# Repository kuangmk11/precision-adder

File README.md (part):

# Precision Adder v2.2
This is a precision CV source and adder. It has four stages, each with an input, an output and a passthru. Each stage's **output** normals down to the next stage's input, so with a single cable into `IN1` the stages cascade and their offsets sum; patching into any `IN` breaks the normal above it. The passthru is a buffered copy of that stage's input, so with nothing patched `PT2` = `OUT1`, `PT3` = `OUT2`, and so on.

Each section provides a different voltage to be added to the input: +/- 2v, +/- 1v, +/- .5833333v (a fifth), +/- .4166666v (a fourth)

## The v2.2 reference build

Everything shipped for the built v2.2 board now lives in [`reference/`](reference/): its
schematic PDF, the three gerber archives, the EasyEDA bill of materials and the photos
above. That revision is finished and is not being changed — the directory is there so the
built design stays available for anyone assembling a v2.2, and as the thing v3 is measured
against.

Two v2.2 documents deliberately stay outside it. [`docs/v2.2-topology.md`](docs/v2.2-topology.md)
is the ladder maths read off the v2.2 schematic, and it is a live input to v3 rather than an
artifact of the old build — `tools/gen_schematic.py` works from it, and `docs/v3-BOM.md`
verifies against it. [`docs/DESIGN-LOG.md`](docs/DESIGN-LOG.md) spans both revisions.

## Available intervals

The switches are SPDT ON-ON, so a stage in the chain always contributes either its positive or its negative offset — there's no center-off. Using the switches alone gives 4 stages x 2 states = **16 combinations** and 13 distinct voltages.

A stage can also be bypassed by patching its `PT` (passthru) into the `IN` of the next stage, feeding that stage's input forward instead of its output. That makes each stage a 3-state element (**+**, **-**, or **bypassed**), for **81 configurations** and **39 distinct voltages**.

The full set is symmetric, so the table below lists magnitudes only — for the negative of any row, flip every `+`/`-` (bypasses stay bypassed). `o` = stage bypassed.

| Semitones | Volts | Interval | Settings (2oct · 1oct · 5th · 4th) |
|---:|---:|---|---|
| 48 | 4.0000 | 4 oct | `+ + + +` |
| 43 | 3.5833 | 3 oct + 5th | `+ + + o` |
| 41 | 3.4167 | 3 oct + 4th | `+ + o +` |
| 38 | 3.1667 | 3 oct + M2 | `+ + + -` |
| 36 | 3.0000 | 3 oct | `+ + o o` · `+ o + +` |
| 34 | 2.8333 | 2 oct + m7 | `+ + - +` |
| 31 | 2.5833 | 2 oct + 5th | `+ + o -` · `+ o + o` |
| 29 | 2.4167 | 2 oct + 4th | `+ + - o` · `+ o o +` |
| 26 | 2.1667 | 2 oct + M2 | `+ o + -` |
| 24 | 2.0000 | 2 oct | `+ + - -` · `+ o o o` · `+ - + +` · `o + + +` |
| 22 | 1.8333 | 1 oct + m7 | `+ o - +` |
| 19 | 1.5833 | 1 oct + 5th | `+ o o -` · `+ - + o` · `o + + o` |
| 17 | 1.4167 | 1 oct + 4th | `+ o - o` · `+ - o +` · `o + o +` |
| 14 | 1.1667 | 1 oct + M2 | `+ - + -` · `o + + -` |
| 12 | 1.0000 | 1 oct | `+ o - -` · `+ - o o` · `o + o o` · `o o + +` |
| 10 | 0.8333 | m7 | `+ - - +` · `o + - +` |
| 7 | 0.5833 | 5th | `+ - o -` · `o + o -` · `o o + o` |
| 5 | 0.4167 | 4th | `+ - - o` · `o + - o` · `o o o +` |
| 2 | 0.1667 | M2 | `o o + -` |
| 0 | 0.0000 | unison | `o o o o` · `+ - - -` · `o + - -` · `o - + +` · `- + + +` |

### The pattern

Every reachable offset is **0, ±2, or ±5 semitones (mod 12)** — unison, M2, 4th, 5th, m7, and their octaves. Within ±48 semitones every such value is reachable *except* ±46. Thirds, tritones, sixths, and single semitones are not available, because a fifth and a fourth can only ever combine to an octave (7+5) or a whole step (7-5).

The usable pitch-class set is therefore the suspended pentatonic `{0, 2, 5, 7, 10}`, spread across a full ±4 octaves in 1/12 V steps.

### Patching notes

- **Leading bypasses are free** — plug your CV into `IN2` / `IN3` / `IN4` instead of `IN1`.
- **Trailing bypasses are free** — take your output from the last active stage's `OUT` instead of `OUT4`.
- **Only interior bypasses cost a cable**: one patch, `PTn` -> `IN(n+1)`, per skipped stage.
- Where a row lists multiple settings, prefer the one with bypasses at the edges — same voltage, fewer cables. For example 2 oct + 4th is `+ + - o` with no cables, versus `+ o o +` with two.

## v3 proposal (unbuilt)

v2.2 is a serial interval adder with a redundant interval set. v3 keeps the cascade, fixes the set, and reorganises the panel around what the cascade is actually good at — stacking intervals into chords.

The interval problem first: because a fifth plus a fourth is exactly an octave (7 + 5 = 12), two of v2.2's four stages collapse into a redundant third. 81 configurations produce only 39 distinct voltages, and the output can never leave the pitch classes `{0, 2, 5, 7, 10}` — no thirds, no sixths, no tritone, no single semitones.

### Four changes

**1. ON-OFF-ON switches.** v2.2 uses SPDT ON-ON, which is why bypassing a stage costs a patch cable. A subminiature ON-OFF-ON is the same footprint at essentially the same price, and the center detent gives each stage a native off position. Every configuration becomes reachable from the front panel with no patching. (Doepfer's A-185-2 has always done it this way — see the comparison below.)

**2. Drop `IN2`-`IN4` and `PT2`-`PT4`.** Outputs normal down to the next input, so with nothing patched `PT2` = `OUT1`, `PT3` = `OUT2`, `PT4` = `OUT3`. Those passthrus are duplicates of the output above them. The extra inputs existed to break the cascade, which the center-off switch now does better. Six jacks were doing the work of two.

**3. Sum three inputs at the front.** `IN1` + `IN2` + `IN3` at unity gain feed the head of the cascade. This is the multi-source summing the module is named for — keyboard plus sequencer plus offset — and it is what the freed panel space buys. `PT` becomes the buffered *sum* of the inputs: an untransposed root that stays put while the cascade transposes everything above it.

**4. Collapse the two octave stages into one, and make stages 2-4 thirds.** Stage 1 becomes a 5-state octave control (±1, ±2, off) from two toggles, freeing a stage. Stages 2 and 3 get a three-position quality switch selecting **4th / maj 3rd / min 3rd**, and stage 4 selects **5th / maj 3rd / min 3rd** — because stacked thirds are how chords are built, and the fifth on the last stage keeps the module's most-used interval one flip away.

### Panel

| | v2.2 | v3 |
|---|---:|---:|
| Jacks | 12 | 8 — `IN1` `IN2` `IN3` `PT` `OUT1`-`OUT4` |
| Switches | 4 | 8 — 2 per stage |
| **Positions** | **16** | **16** |

Same density as the board already built. No rotary, no new mechanical problem.

**This is a new panel, not v2.2's reused.** Earlier v3 drafts kept every v2.2 hole
position and only reassigned diameters, which forced the four outputs into two shared
rows. Grouping each stage instead — its two switches and its own output, boxed together —
needs six evenly spaced rows below the inputs, so the positions are refitted. The v3 main
board is new anyway.

Panel and drawing are generated by [`tools/gen_panel.py`](tools/gen_panel.py) from one
layout table, so they cannot disagree:

```sh
python3 tools/gen_panel.py            # writes the .kicad_pcb and the .svg, with a clearance report
python3 tools/gen_panel.py --table    # the hole schedule below
```

- [`docs/v3-panel.kicad_pcb`](docs/v3-panel.kicad_pcb) — board outline, holes and mounting
  slots on `Edge.Cuts`, silkscreen on `F.SilkS`. Holes are `Edge.Cuts` circles, so the fab
  routes rather than drills them; swap to NPTH pads if your fab prefers.
- [`docs/v3-panel.svg`](docs/v3-panel.svg) — the same geometry at 1:1 (1 unit = 1 mm,
  20 × 128.5 mm), for printing and review. The grey rings are hardware footprints — 8 mm
  Thonkiconn nut, 7.5 mm toggle nut — shown for clearance checking, not artwork, and not
  in the KiCad output.

Conventions — lettering, marks, label placement, mounting — are in
[`PANEL_STYLE_v1.02.md`](PANEL_STYLE_v1.02.md).

#### How it reads

Four jacks at the top: three summed inputs and `SUM`, the buffered sum that `PT` becomes.
`SUM` is an output, so it carries the ring — the panel's only closed circle, which is what
lets direction read at a glance. The ring has to clear the 8 mm nut to be visible at all,
and a 20 mm panel carrying two 8 mm nuts has 4 mm of slack in total, so at r 4.4 it ends up
0.28 mm from the cut on the outboard side. Still on the board, but well inside the 0.6 mm
edge margin, and a fab may trim the outer edge of it. Taken deliberately: a broken ring
reads worse than a clipped one. Below them, **four boxed groups, one per stage — polarity
switch, selector switch, that stage's output.** Each stage now owns its output, which the
old shared-row layout could not manage.

**Arrows trace the cascade** across the top pair, down into the bottom-left group, and
across the bottom pair — the order the stages actually sum in. The middle leg cannot be a
straight diagonal: about 4 mm of clear band between the box rows against a 10.8 mm column
pitch would need a 15° line, and the house routing is 0°, 90° and 45° only. So it drops,
takes a 45° knee, runs the band and turns down into the group it feeds. Where an arrow
crosses a box outline the outline is broken, the same way a group name breaks it.

`OUT1`–`OUT4` do not repeat the ring. Each already sits inside a named box that says which
stage it belongs to, and the style guide's rule against a second closed circle is what
keeps `SUM`'s ring meaningful. If you would rather every output ring, it is one line in the
generator.

Within a group: `+` above the polarity toggle, `−` below it, and **`0` beside its centre
detent**. The selector's two throws are labelled above and below it the same way.

That `0` matters more than it looks. A selector displays a value at all times, so without
it the panel reads as though a stage adds its interval even when the stage is switched off
— and the polarity toggle's centre, not the selector's, is what turns a stage off. One rule
covers both toggles now: **a three-position toggle's centre value is marked in the strip
between its nut and the box edge.** `OCT`'s magnitude switch is two-position and has no
centre, so it carries no such mark.

It is also why a plain fifth is one flip. At rest every polarity toggle is centred and the
module passes through untouched, whatever the selectors show; move stage 4's polarity to
`+` and its selector is already sitting on the `5`.

**The selector's centre detent carries the stage's odd interval** — the 4th on the two
`3RD` stages, the 5th on `5TH` — and the two throws are the two thirds, `MAJ` and `MIN`.
That is partly ergonomic, since the thirds are the pair you reach for when building a
chord, and partly forced: the centre mark is the only one with nowhere to go but the
1.2 mm strip between the toggle nut and the box, where a single character fits and two do
not. It is set at 1.0 mm, below the house 1.6 mm minimum, and is the one deliberate
exception on the panel.

#### Hole schedule

Origin top-left, millimetres, Y down — the drawing's own frame, not the old gerbers'.

| Y (mm) | X (mm) | Ø | What |
|---:|---:|---:|---|
| 16.60 | 4.80 | 6.0 | IN1 |
| 16.60 | 15.20 | 6.0 | IN2 |
| 28.60 | 4.80 | 6.0 | IN3 |
| 28.60 | 15.20 | 6.0 | SUM (output, ringed) |
| 44.80 | 4.80 | 5.0 | OCT polarity  +/o/− |
| 44.80 | 15.20 | 5.0 | 3RD polarity  +/o/− |
| 57.80 | 4.80 | 5.0 | OCT select  1/2 |
| 57.80 | 15.20 | 5.0 | 3RD select  MAJ/MIN (detent 4) |
| 68.80 | 4.80 | 6.0 | OUT1 |
| 68.80 | 15.20 | 6.0 | OUT2 |
| 88.00 | 4.80 | 5.0 | 3RD polarity  +/o/− |
| 88.00 | 15.20 | 5.0 | 5TH polarity  +/o/− |
| 101.00 | 4.80 | 5.0 | 3RD select  MAJ/MIN (detent 4) |
| 101.00 | 15.20 | 5.0 | 5TH select  MAJ/MIN (detent 5) |
| 112.00 | 4.80 | 6.0 | OUT3 |
| 112.00 | 15.20 | 6.0 | OUT4 |
| 3.00 | 12.50 | 6.4×3.2 | mounting slot, obround |
| 125.50 | 7.50 | 6.4×3.2 | mounting slot, obround |

Mounting follows the style guide's ≤ 6 HP rule: one 6.4 × 3.2 mm horizontal slot top-right
and one bottom-left, so the module can slide ±1.6 mm to meet its neighbours and cannot
pivot on a single screw per rail. v2.2's round Ø3.2 holes do not carry over.

#### What the generator checks, and what it cannot

`gen_panel.py` refuses to write if anything overlaps, and reports the tightest clearance in
each category. Currently: **0.15 mm** text-to-nut, **0.64 mm** text-to-text, **0.15 mm**
text-to-silk, **0.42 mm** text-to-ring, **0.60 mm** silk-to-edge, **1.40 mm** of material
at the worst hole, and **2.40 mm** between the closest two nuts. `SUM`'s ring is exempted
from the edge margin and reported separately, so the exception stays visible instead of
being absorbed into a looser rule.

Those come from a stroke-glyph model that assumes ink fills 0.62 em of each character
cell — conservative for the KiCad stroke font, but still a model. **KiCad's own DRC passes
with 0 violations and 0 unconnected items** (`tools/kicad-check.sh`), and the board plots
correctly from KiCad, mounting slots and all.

The two toggles in a group are 13.0 mm apart, leaving 5.5 mm between their nuts — up from
4.9 mm in the row-based draft, but still unproven on this hardware, since v2.2 stacks no
toggles at all. Print the SVG at 100%, check it measures 20 × 128.5 mm, and try the pairs
with real fingers.

### Schematic

[`docs/v3-adder.kicad_sch`](docs/v3-adder.kicad_sch), generated by
[`tools/gen_schematic.py`](tools/gen_schematic.py) from a netlist table:

```sh
python3 tools/gen_schematic.py             # writes the .kicad_sch, with a design report
python3 tools/gen_schematic.py --bom       # bill of materials
python3 tools/gen_schematic.py --netlist   # every net and what is on it
```

**It is a scaffold, not a finished drawing.** Connectivity is complete and correct;
placement is a plain grid, and every connection is made with a net label on a short pin stub
rather than by routing wires. That is deliberate — label-based connectivity cannot be got
subtly wrong the way routed wires can, and rearranging symbols in KiCad afterwards breaks
nothing. Expect to spend time on layout, not on wiring.

Topology follows [`docs/v2.2-topology.md`](docs/v2.2-topology.md). The reference block, the
power block and the summing topology are v2.2's, unchanged. 102 parts, 72 nets, 12 op-amp
channels across three OPA4196 — 11 used, one spare tied off as a follower.

**Only the lower ladder segments need to be precise.** A tap's voltage is set by the ratio
of the segments below it to the whole chain, and the trimmer sits in series at the top, so
the top segment's absolute value is absorbed by trimming — which is why the BOM shows
5.5k, 24.5k and 22.5k and why that does not matter. Use the nearest E96 part and let the
trimmer take up the difference. What does matter is the ratio between the small segments
(1k, 3k, 12k), and that is where hand-matched parts earn their keep.

Alongside the schematic the generator writes `adder.kicad_sym`, `v3-adder.kicad_pro` and a
`sym-lib-table`, so the project opens with its symbol library resolved rather than warning
once per symbol.

**KiCad's own ERC passes with 0 errors.** Run it yourself:

```sh
KICAD_CLI="/path/to/kicad-cli" tools/kicad-check.sh    # ERC, DRC and plots into .kicadcheck/
```

The 23 remaining ERC warnings are all `footprint_link_issues` on the custom parts — jacks,
toggles, trimmers, ferrites, the Eurorack header. Those footprints are yours to supply, and
a name that does not resolve is a more honest placeholder than a wrong one that does. Stock
KiCad footprints are used everywhere they exist, so the passives, op-amps, regulators and
diodes resolve on any install.

### Bill of materials

[`docs/v3-BOM.md`](docs/v3-BOM.md) is the parts list, with the tolerance reasoning for every
line. [`docs/BOM_v3_DigiKey.csv`](docs/BOM_v3_DigiKey.csv) alongside it is an upload-ready
DigiKey list covering 93 of the parts; its sourcing notes are the last section of `v3-BOM.md`.

Three things are worth knowing before ordering. The **E24 values this design depends on are
stocked in 0.1 %** — Panasonic's ERA-8 series has both the 3.00k and the 12.0k, so choosing E24
over E96 for the exact 3:1 ratio costs nothing in availability. The **ON-ON-ON DPDT has no
DigiKey equivalent** in this form factor and must come from a synth DIY shop, along with the
jacks and the axial ferrites. And **C9/C10 need a decision**: the MnO2 tantalum that satisfies
the ESR requirement is a surface-mount part, which does not fit the through-hole footprint the
BOM currently specifies for them.

#### Switches

Taiway series 200 subminiature throughout — `T1` actuator, `B1` bushing, `M2` PC thru-hole,
`Q` silver, `E` epoxy:

| Function | Part | Used for |
|---|---|---|
| SPDT ON-OFF-ON | `200-MSP3-T1B1M2QE` | polarity, ×4 |
| SPDT ON-ON | `200-MSP1-T1B1M2QE` | `OCT` magnitude, ×1 |
| DPDT ON-ON-ON | `200-MDP6-T1B1M2QE` | quality selectors, ×3 |

The `B1` bushing is **10-48 UNS, Ø4.80** and Taiway's recommended panel hole is **Ø4.95** —
the panel's Ø5.0 is right. There is also an optional 4.55 mm flat in the hole for
anti-rotation, which the panel does not cut, so the switches are held by nut torque alone.

**A DPDT ON-ON-ON is a 1-of-3 selector only if you cascade its poles.** Pins 1‑2‑3 are pole
A with 2 common, 4‑5‑6 are pole B with 5 common. Pole A's common is the output; one of its
throws is a tap outright, the other feeds pole B's common, and pole B picks between the
remaining two. Tying the commons together instead would short two ladder taps in every
position.

`MDP-6`'s contact sequence, from Taiway:

| Position | Contacts |
|---|---|
| 1 | `2-3, 5-6` |
| 2 (centre) | `2-3, 5-4` |
| 3 | `2-1, 5-4` |

`ONONON_VARIANT = 1` in `tools/gen_schematic.py` encodes exactly this. `check_selector()`
walks each selector through all three positions from that table and asserts the output
reaches the intended tap and **exactly one** tap — the property that makes the cascade
trustworthy, since getting it wrong shorts two points of a resistor ladder rather than
failing loudly. Setting the variant to 2 makes it fail at the centre detent, as it should.

PC-mount terminals are on a **5.08 × 2.54 mm** grid, six pins, numbered 6‑5‑4 down one
column and 3‑2‑1 down the other.

**Orientation does not matter.** The body is symmetric, so fitting it 180° round swaps
diagonally opposite pads (6↔1, 5↔2, 4↔3) *and* reverses the lever — and those two cancel
exactly. Read against the board's own pad numbers from lever-up to lever-down, the sequence
is unchanged. The pin numbers on a reversed part are wrong; its behaviour is not.
`check_rotation_symmetry()` asserts this against the contact table, so it stays true if the
table is ever edited.

The generator additionally checks, before writing: every `lib_id` resolves as a full
`library:name` string and every instantiated unit has a matching body; every pin coordinate
read back out of the written file lands on a wire endpoint, so the label stubs really do
attach; no pin is unconnected; no net has fewer than two connections; no reference is used
twice and no pin appears on two nets; and every ladder tap computes to its interval voltage
exactly with the trimmer centred.

### Stages

Read the selector column as **up / _centre detent_ / down**, which is how the panel is
marked: the two throws are the thirds, the detent is the stage's odd interval.

| Stage | Panel group | Control | Selects — up / _detent_ / down | Values | Volts |
|---|---|---|---|---|---|
| 1 | `OCT` | on-off-on + `1/2` on-on | 1 oct / — / 2 oct | ±12, ±24 st | 1.000000 / 2.000000 |
| 2 | `3RD` | on-off-on + quality on-on-on | M3 / _4th_ / m3 | ±4, ±5, ±3 st | 0.333333 / 0.416667 / 0.250000 |
| 3 | `3RD` | on-off-on + quality on-on-on | M3 / _4th_ / m3 | ±4, ±5, ±3 st | 0.333333 / 0.416667 / 0.250000 |
| 4 | `5TH` | on-off-on + quality on-on-on | M3 / _**5th**_ / m3 | ±4, ±7, ±3 st | 0.333333 / 0.583333 / 0.250000 |

The values are unchanged from earlier drafts — only which throw carries which. Stage 1's
magnitude switch is a two-position ON-ON, so it has no detent.

Stage 4 takes a **5th** where stages 2 and 3 take a 4th. That buys back the one-switch fifth — the module's most-used interval — and on the chord side it turns stage 4 into an extension selector, since stages 2 and 3 have already built the triad by the time the signal reaches it.

**1715 configurations, 83 distinct voltages, fully chromatic across ±41 semitones (±3.42 octaves), all 12 pitch classes.**

### Chords

The cascade means each output is a running sum, so `OUT1`-`OUT4` are stacked intervals, with `PT` available as an untransposed root beneath them. **Stages 2 and 3 set the triad; stage 4 sets the extension.**

| Triad (st2 + st3) | st4 = m3 | st4 = M3 | st4 = 5th |
|---|---|---|---|
| M3 + m3 — **major** | dominant 7th | major 7th | add9 |
| m3 + M3 — **minor** | minor 7th | minor-major 7th | minor add9 |
| m3 + m3 — **diminished** | diminished 7th | half-diminished | dim add b9 |
| M3 + M3 — **augmented** | augmented maj7 | augmented (8ve) | augmented #9 |

Twelve voicings from three switches, and the triad is already correct on `OUT1`-`OUT3` before stage 4 is touched. The 4th position on stages 2 and 3 adds sus and quartal voicings on top of that.

The `OCT` stage transposes the whole chord while `PT` holds the original root — so a pedal tone stays put underneath a transposed voicing.

This is what the old `{octave, 5th, 4th, maj 3rd}` set could not do: fifths and fourths do not stack into chords.

### Transposition chart

Taking `OUT4` as a single transposed voice. `o` = switch centered. Within any octave the settings are identical, so the `OCT` stage handles everything above; negative intervals are the mirror image.

| Semitones | Volts | Interval | OCT | st2 | st3 | st4 | Flips |
|---:|---:|---|:---:|:---:|:---:|:---:|---:|
| 0 | 0.0000 | unison | `o` | `o` | `o` | `o` | 0 |
| 1 | 0.0833 | min 2nd | `o` | `o` | `+4th` | `-M3` | 2 |
| 2 | 0.1667 | maj 2nd | `o` | `o` | `+4th` | `-m3` | 2 |
| 3 | 0.2500 | min 3rd | `o` | `o` | `o` | `+m3` | 1 |
| 4 | 0.3333 | maj 3rd | `o` | `o` | `o` | `+M3` | 1 |
| 5 | 0.4167 | 4th | `o` | `o` | `+4th` | `o` | 1 |
| 6 | 0.5000 | tritone | `o` | `o` | `+m3` | `+m3` | 2 |
| 7 | 0.5833 | 5th | `o` | `o` | `o` | `+5th` | **1** |
| 8 | 0.6667 | min 6th | `o` | `o` | `+4th` | `+m3` | 2 |
| 9 | 0.7500 | maj 6th | `o` | `o` | `+4th` | `+M3` | 2 |
| 10 | 0.8333 | min 7th | `o` | `o` | `+m3` | `+5th` | 2 |
| 11 | 0.9167 | maj 7th | `o` | `o` | `+M3` | `+5th` | 2 |
| 12 | 1.0000 | octave | `+1` | `o` | `o` | `o` | 1 |

Every interval up to the octave is one or two switch positions, and the octave, 4th, 5th, maj 3rd and min 3rd are all single flips. The remaining rows read as stacks — a tritone is two minor thirds, a major 7th is a major third over a fifth.

### Build notes

- **BOM:** 4x `SUBMINI_SPDT ON-OFF-ON` (polarity, one per stage), 3x `ON-ON-ON` DPDT (quality, stages 2-4), 1x `ON-ON` (octave magnitude). 8 jacks instead of 12.
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
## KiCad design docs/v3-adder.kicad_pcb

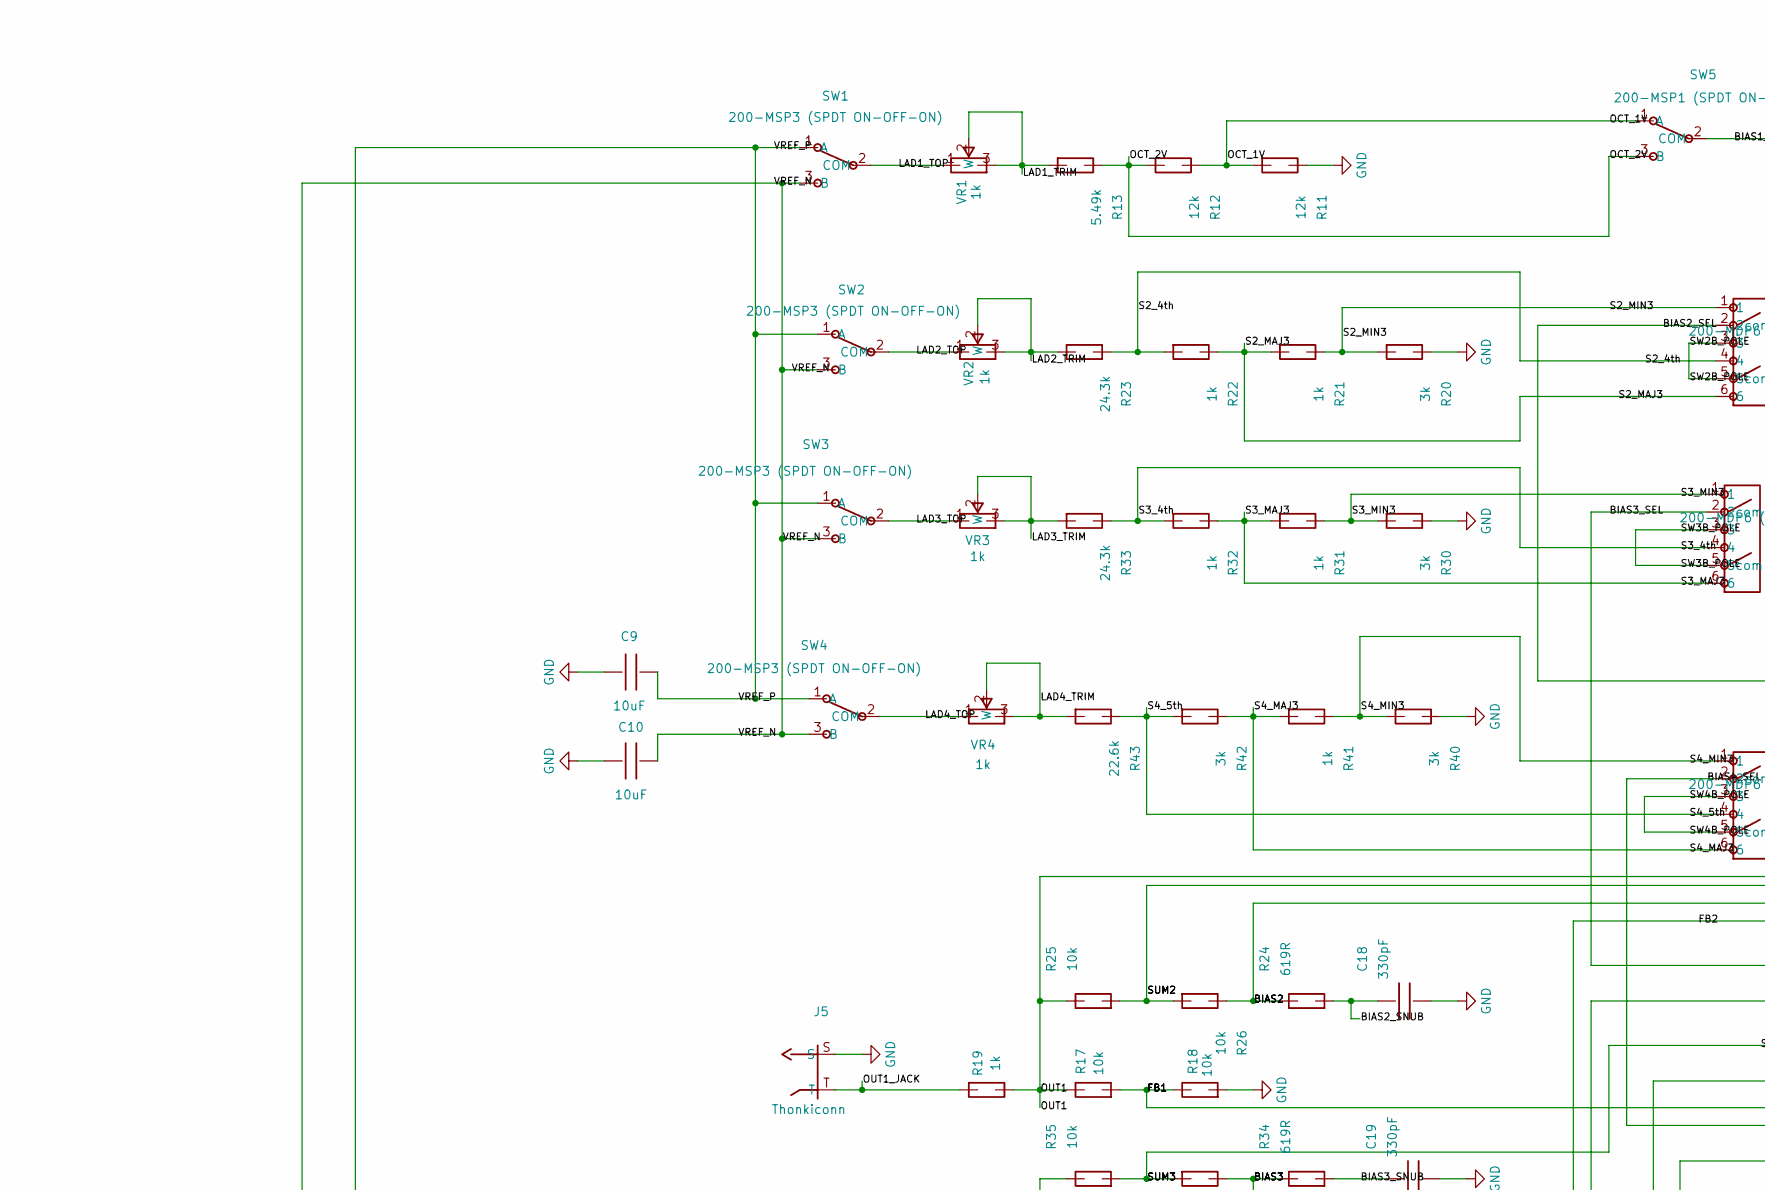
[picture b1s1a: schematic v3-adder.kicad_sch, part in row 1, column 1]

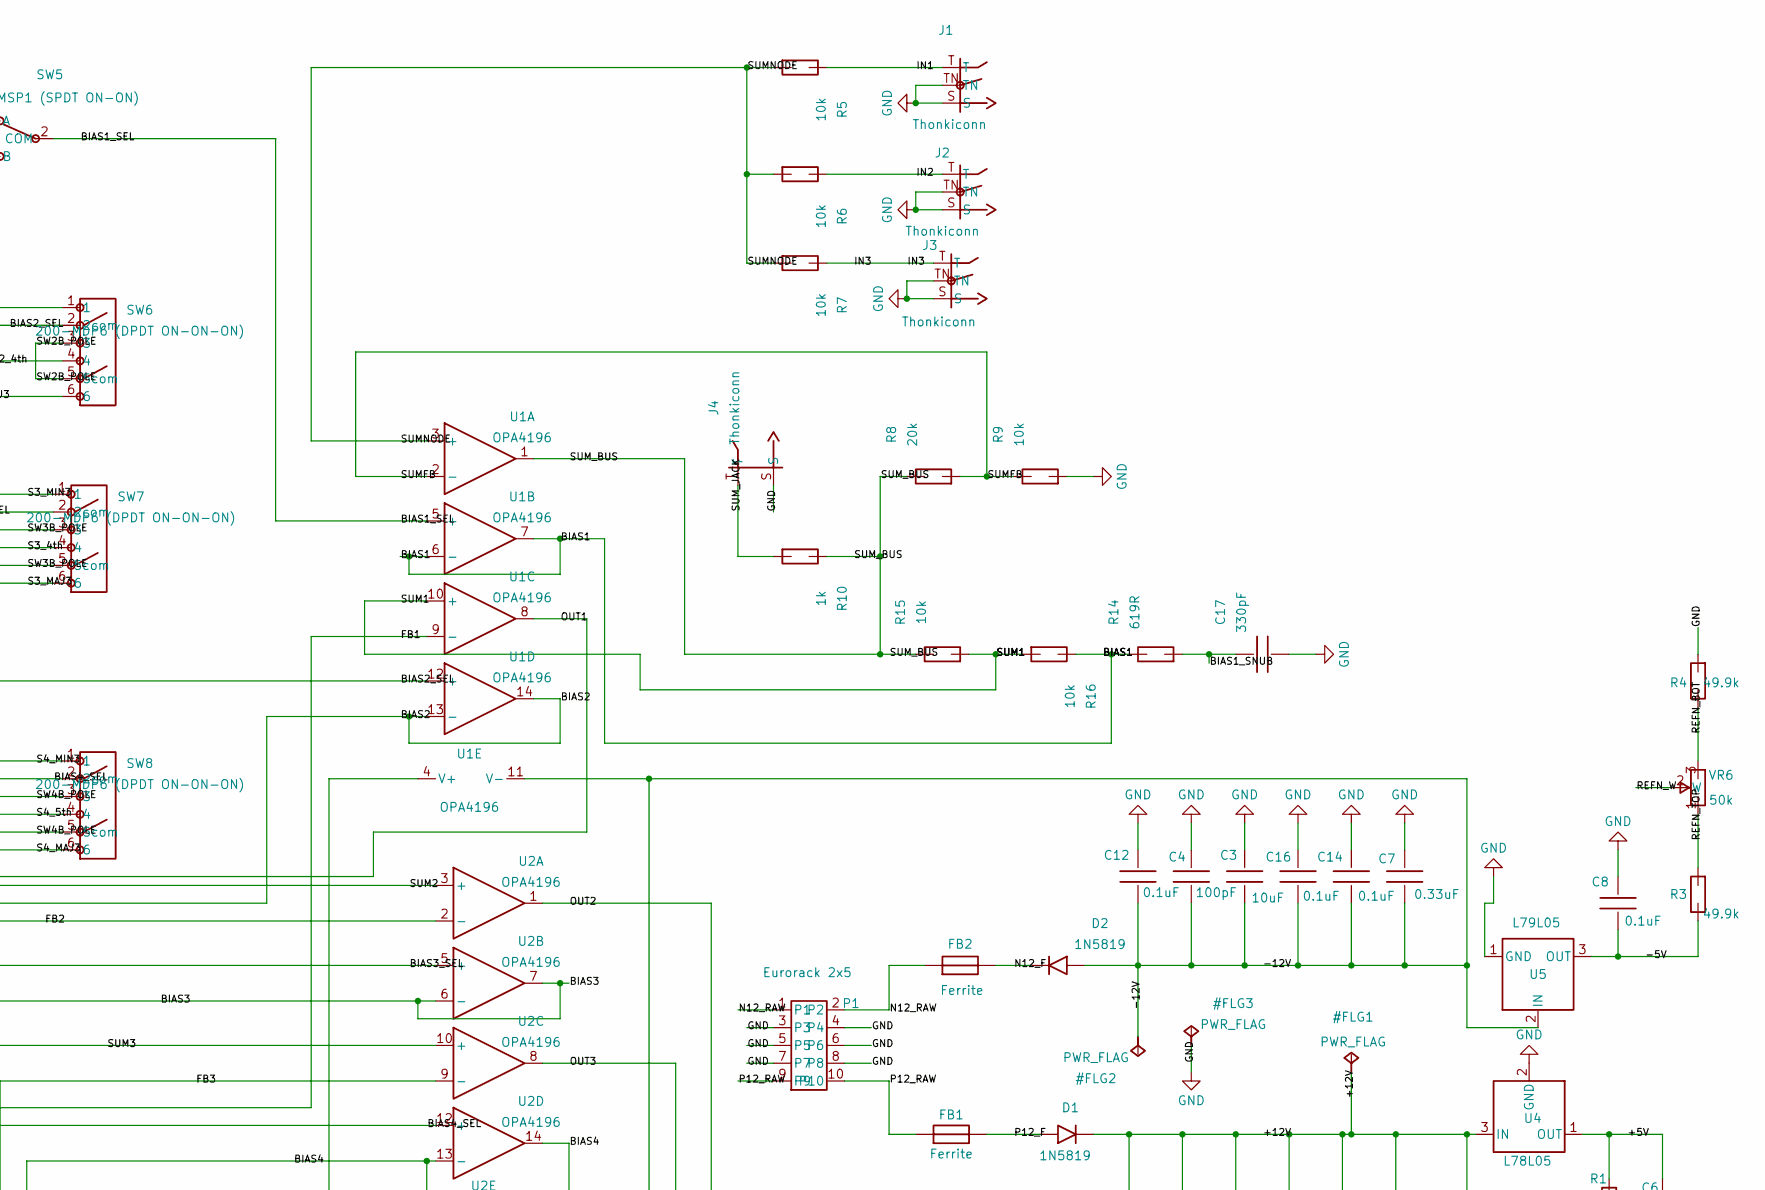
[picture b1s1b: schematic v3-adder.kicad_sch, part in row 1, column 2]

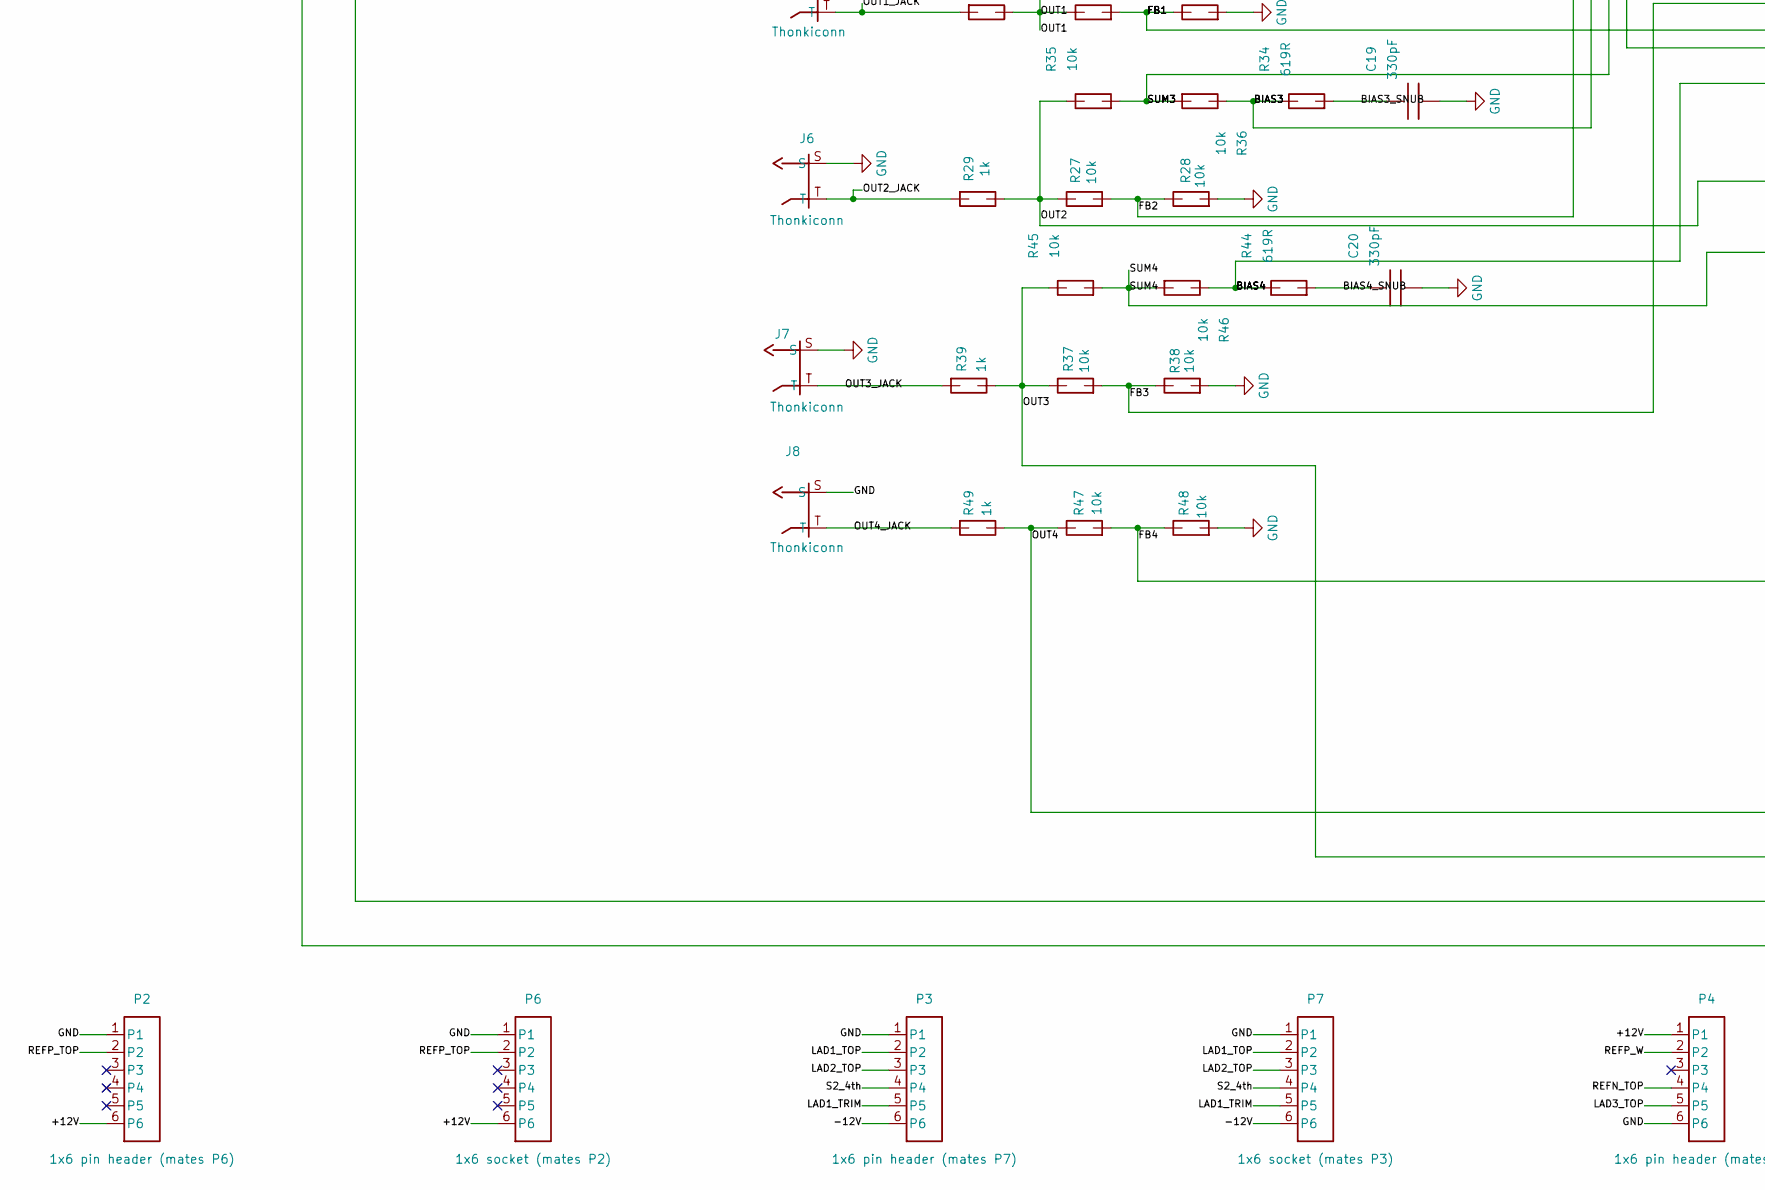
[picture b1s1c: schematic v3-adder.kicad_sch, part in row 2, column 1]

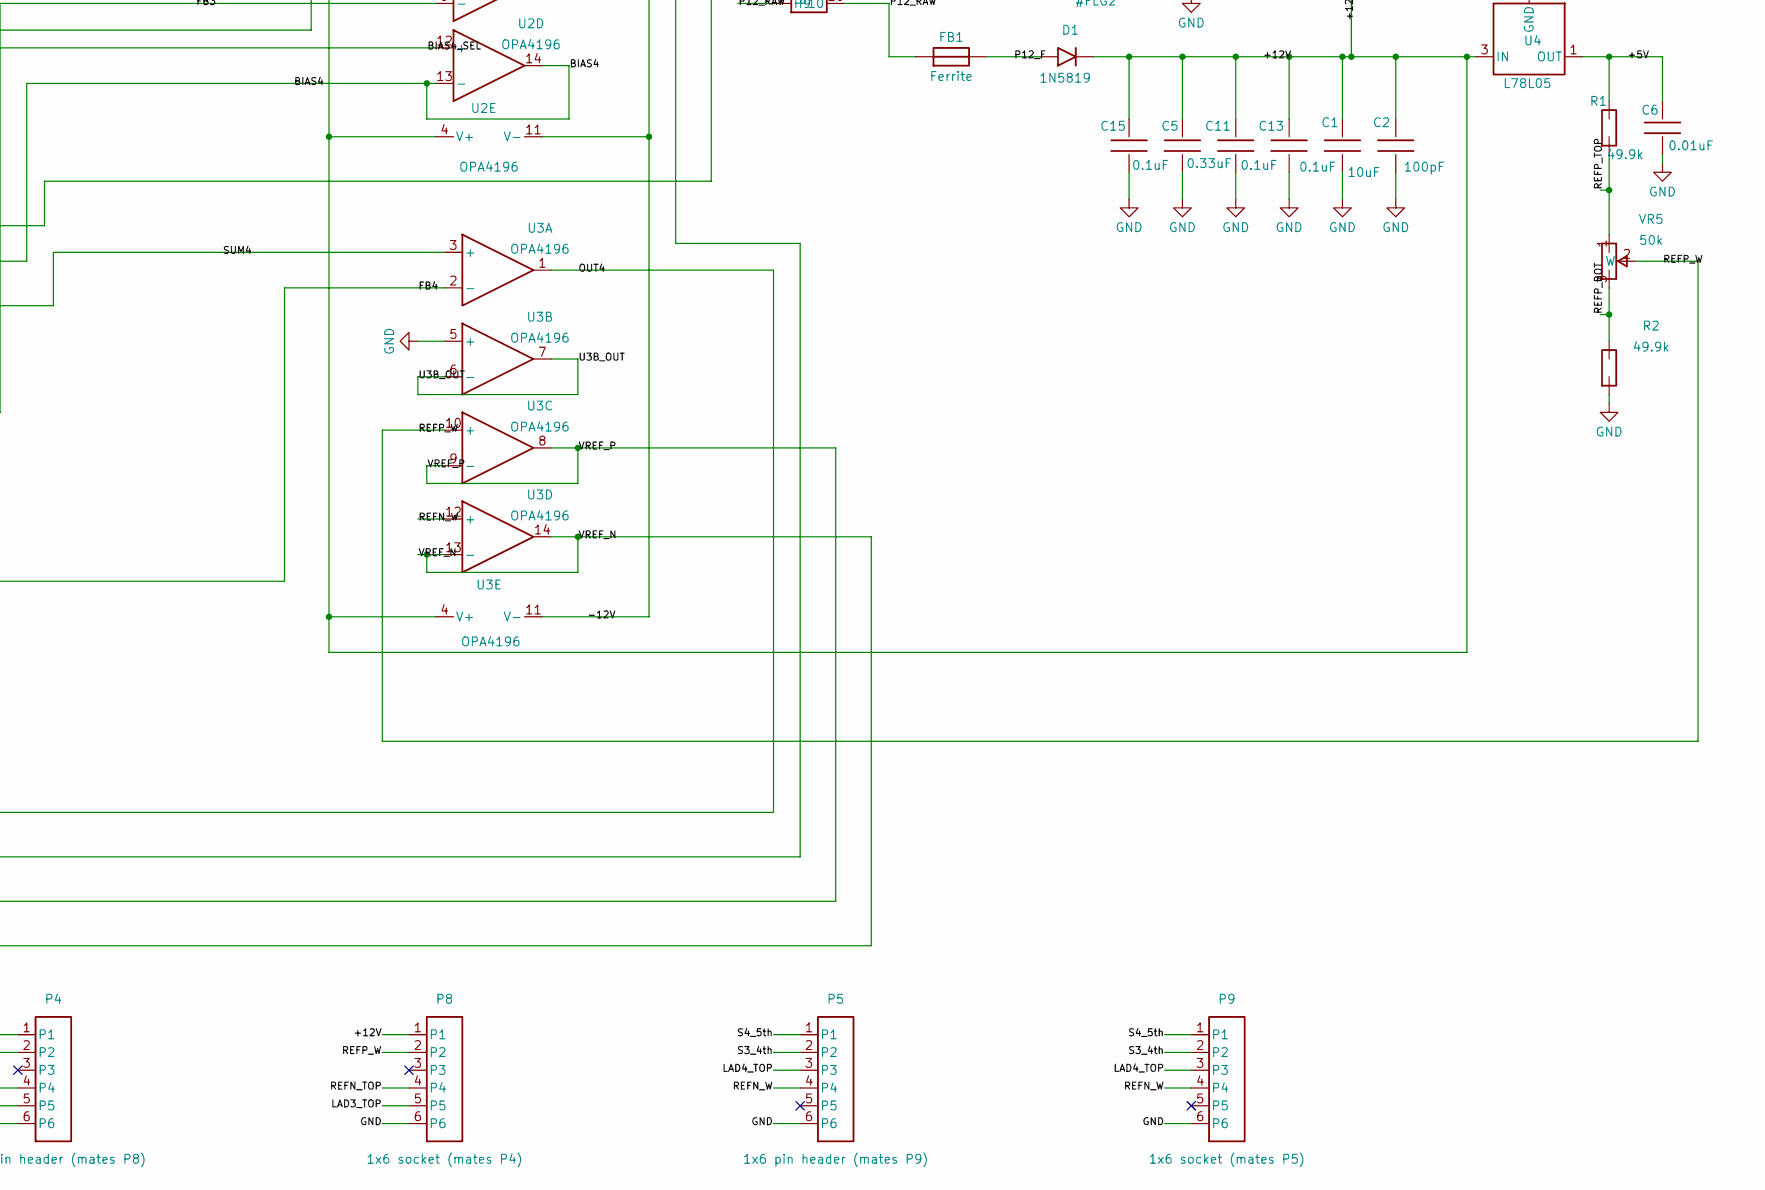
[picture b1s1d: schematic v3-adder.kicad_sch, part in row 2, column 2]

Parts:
C1, C3, C9, C10: 10uF; CP_Radial_D5.0mm_P2.00mm
C2, C4: 100pF; C_1206_3216Metric
C5, C7: 0.33uF; C_1206_3216Metric
C6: 0.01uF; C_1206_3216Metric
C8, C11, C12, C13, C14, C15, C16: 0.1uF; C_1206_3216Metric
C17, C18, C19, C20: 330pF; C_1206_3216Metric
D1, D2: 1N5819; D_DO-41_SOD81_P10.16mm_Horizontal
FB1, FB2: Ferrite; R_Axial_DIN0207_L6.3mm_D2.5mm_P7.62mm_Horizontal
J1, J2, J3, J4, J5, J6, J7, J8: Thonkiconn; Thonkiconn_PJ301M
P1: Eurorack 2x5; IDC-Header_2x05_P2.54mm_Vertical
P2: 1x6 pin header (mates P6); PinHeader_1x06_P2.54mm_Vertical
P3: 1x6 pin header (mates P7); PinHeader_1x06_P2.54mm_Vertical
P4: 1x6 pin header (mates P8); PinHeader_1x06_P2.54mm_Vertical
P5: 1x6 pin header (mates P9); PinHeader_1x06_P2.54mm_Vertical
P6: 1x6 socket (mates P2); PinSocket_1x06_P2.54mm_Vertical
P7: 1x6 socket (mates P3); PinSocket_1x06_P2.54mm_Vertical
P8: 1x6 socket (mates P4); PinSocket_1x06_P2.54mm_Vertical
P9: 1x6 socket (mates P5); PinSocket_1x06_P2.54mm_Vertical
R1, R2, R3, R4: 49.9k; R_1206_3216Metric
R5, R6, R7, R9, R15, R16, R17, R18, R25, R26, R27, R28, R35, R36, R37, R38, R45, R46, R47, R48: 10k; R_1206_3216Metric
R8: 20k; R_1206_3216Metric
R10, R19, R21, R22, R29, R31, R32, R39, R41, R49: 1k; R_1206_3216Metric
R11, R12: 12k; R_1206_3216Metric
R13: 5.49k; R_1206_3216Metric
R14, R24, R34, R44: 619R; R_1206_3216Metric
R20, R30, R40, R42: 3k; R_1206_3216Metric
R23, R33: 24.3k; R_1206_3216Metric
R43: 22.6k; R_1206_3216Metric
SW1, SW2, SW3, SW4: 200-MSP3 (SPDT ON-OFF-ON); SW_Taiway_200_SPDT
SW5: 200-MSP1 (SPDT ON-ON); SW_Taiway_200_SPDT
SW6, SW7, SW8: 200-MDP6 (DPDT ON-ON-ON); SW_Taiway_200_DPDT
U1, U2, U3: OPA4196; SOIC-14_3.9x8.7mm_P1.27mm
U4: L78L05; TO-92_Inline
U5: L79L05; TO-92_Inline
VR1, VR2, VR3, VR4: 1k; Potentiometer_Bourns_3296W_Vertical
VR5, VR6: 50k; Potentiometer_Bourns_3296W_Vertical

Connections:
/+5V: C6.1, R1.1, U4.1 (OUT)
/+12V: C1.1, C2.1, C5.1, C11.1, C13.1, C15.1, D1.1 (K), P2.6, P4.1, P6.6, P8.1, U1.4 (V+), U2.4 (V+), U3.4 (V+), U4.3 (IN)
/-5V: C8.1, R3.1, U5.3 (OUT)
/-12V: C3.1, C4.1, C7.1, C12.1, C14.1, C16.1, D2.2 (A), P3.6, P7.6, U1.11 (V-), U2.11 (V-), U3.11 (V-), U5.2 (IN)
/BIAS1: R14.1, R16.1, U1.6 (-), U1.7
/BIAS1_SEL: SW5.2 (COM), U1.5 (+)
/BIAS1_SNUB: C17.1, R14.2
/BIAS2: R24.1, R26.1, U1.13 (-), U1.14
/BIAS2_SEL: SW6.2 (2com), U1.12 (+)
/BIAS2_SNUB: C18.1, R24.2
/BIAS3: R34.1, R36.1, U2.6 (-), U2.7
/BIAS3_SEL: SW7.2 (2com), U2.5 (+)
/BIAS3_SNUB: C19.1, R34.2
/BIAS4: R44.1, R46.1, U2.13 (-), U2.14
/BIAS4_SEL: SW8.2 (2com), U2.12 (+)
/BIAS4_SNUB: C20.1, R44.2
/FB1: R17.2, R18.1, U1.9 (-)
/FB2: R27.2, R28.1, U2.2 (-)
/FB3: R37.2, R38.1, U2.9 (-)
/FB4: R47.2, R48.1, U3.2 (-)
/IN1: J1.T, R5.1
/IN2: J2.T, R6.1
/IN3: J3.T, R7.1
/LAD1_TOP: P3.2, P7.2, SW1.2 (COM), VR1.1
/LAD1_TRIM: P3.5, P7.5, R13.2, VR1.2 (W_2), VR1.3
/LAD2_TOP: P3.3, P7.3, SW2.2 (COM), VR2.1
/LAD2_TRIM: R23.2, VR2.2 (W_2), VR2.3
/LAD3_TOP: P4.5, P8.5, SW3.2 (COM), VR3.1
/LAD3_TRIM: R33.2, VR3.2 (W_2), VR3.3
/LAD4_TOP: P5.3, P9.3, SW4.2 (COM), VR4.1
/LAD4_TRIM: R43.2, VR4.2 (W_2), VR4.3
/N12_F: D2.1 (K), FB2.2
/N12_RAW: FB2.1, P1.1, P1.2
/OCT_1V: R11.2, R12.1, SW5.1 (A)
/OCT_2V: R12.2, R13.1, SW5.3 (B)
/OUT1: R17.1, R19.1, R25.1, U1.8
/OUT1_JACK: J5.T, R19.2
/OUT2: R27.1, R29.1, R35.1, U2.1
/OUT2_JACK: J6.T, R29.2
/OUT3: R37.1, R39.1, R45.1, U2.8
/OUT3_JACK: J7.T, R39.2
/OUT4: R47.1, R49.1, U3.1
/OUT4_JACK: J8.T, R49.2
/P12_F: D1.2 (A), FB1.2
/P12_RAW: FB1.1, P1.9, P1.10
/REFN_BOT: R4.1, VR6.3
/REFN_TOP: P4.4, P8.4, R3.2, VR6.1
/REFN_W: P5.4, P9.4, U3.12 (+), VR6.2 (W_2)
/REFP_BOT: R2.1, VR5.3
/REFP_TOP: P2.2, P6.2, R1.2, VR5.1
/REFP_W: P4.2, P8.2, U3.10 (+), VR5.2 (W_2)
/S2_4th: P3.4, P7.4, R22.2, R23.1, SW6.4
/S2_MAJ3: R21.2, R22.1, SW6.6
/S2_MIN3: R20.2, R21.1, SW6.1
/S3_4th: P5.2, P9.2, R32.2, R33.1, SW7.4
/S3_MAJ3: R31.2, R32.1, SW7.6
/S3_MIN3: R30.2, R31.1, SW7.1
/S4_5th: P5.1, P9.1, R42.2, R43.1, SW8.4
/S4_MAJ3: R41.2, R42.1, SW8.6
/S4_MIN3: R40.2, R41.1, SW8.1
/SUM1: R15.2, R16.2, U1.10 (+)
/SUM2: R25.2, R26.2, U2.3 (+)
/SUM3: R35.2, R36.2, U2.10 (+)
/SUM4: R45.2, R46.2, U3.3 (+)
/SUMFB: R8.2, R9.1, U1.2 (-)
/SUMNODE: R5.2, R6.2, R7.2, U1.3 (+)
/SUM_BUS: R8.1, R10.1, R15.1, U1.1
/SUM_JACK: J4.T, R10.2
/SW2B_POLE: SW6.3, SW6.5 (5com)
/SW3B_POLE: SW7.3, SW7.5 (5com)
/SW4B_POLE: SW8.3, SW8.5 (5com)
/U3B_OUT: U3.6 (-), U3.7
/VREF_N: C10.1, SW1.3 (B), SW2.3 (B), SW3.3 (B), SW4.3 (B), U3.13 (-), U3.14
/VREF_P: C9.1, SW1.1 (A), SW2.1 (A), SW3.1 (A), SW4.1 (A), U3.8, U3.9 (-)
GND: C1.2, C2.2, C3.2, C4.2, C5.2, C6.2, C7.2, C8.2, C9.2, C10.2, C11.2, C12.2, C13.2, C14.2, C15.2, C16.2, C17.2, C18.2, C19.2, C20.2, J1.S, J1.TN, J2.S, J2.TN, J3.S, J3.TN, J4.S, J5.S, J6.S, J7.S, J8.S, P1.3, P1.4, P1.5, P1.6, P1.7, P1.8, P2.1, P3.1, P4.6, P5.6, P6.1, P7.1, P8.6, P9.6, R2.2, R4.2, R9.2, R11.1, R18.2, R20.1, R28.2, R30.1, R38.2, R40.1, R48.2, U3.5 (+), U4.2 (GND), U5.1 (GND)

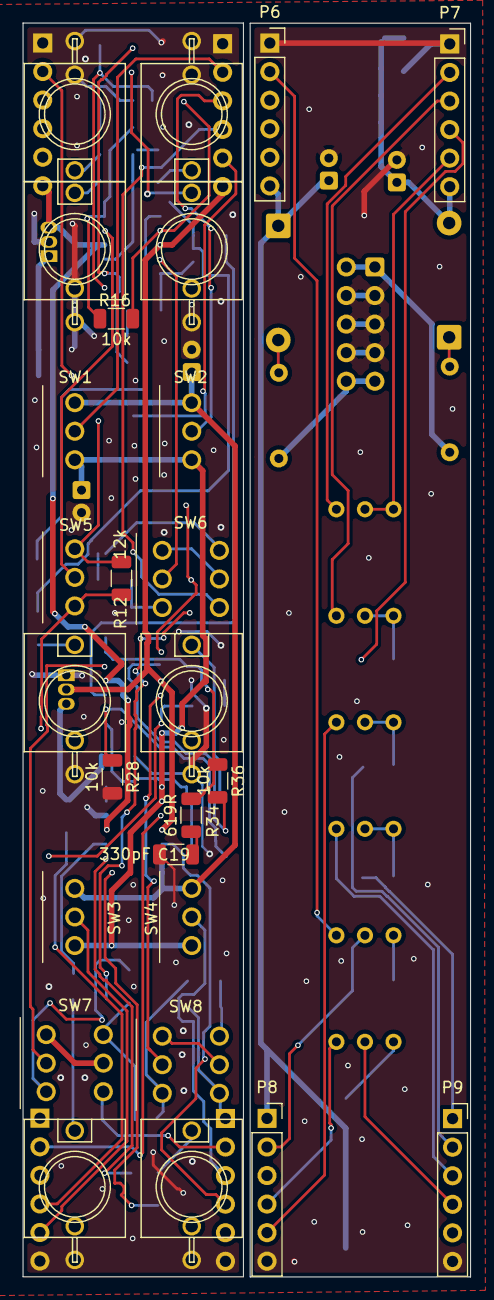
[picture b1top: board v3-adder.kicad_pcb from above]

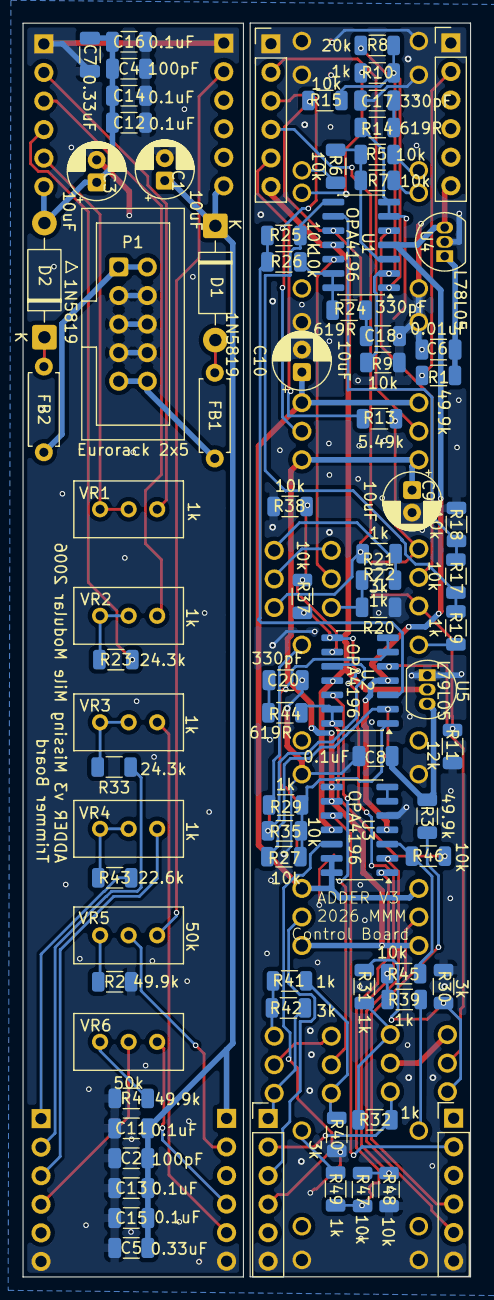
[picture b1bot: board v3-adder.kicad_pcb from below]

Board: 2 copper layers, 39.8 x 111.5 mm, 109 parts (83 on the bottom side), 75 nets.

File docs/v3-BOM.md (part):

# v3 bill of materials

Built for **hand assembly**: 1206 everywhere an SMD part is used, and through-hole kept for
anything that was already through-hole. 1206 is the largest size these values are commonly
stocked in, and the OPA4196's SOIC-14 is the largest package it comes in.

101 components. Values verified against the ladder maths in `v2.2-topology.md` — every
interval tap lands **exact to 0.000 cents** with these parts.

## Resistors

All 1206, `Resistor_SMD:R_1206_3216Metric`.

### 0.1 % — 32 parts

These set pitch directly. The per-stage trimmer corrects the chain's overall scale but
**not the ratios between taps**, so tolerance here is not recoverable.

| Qty | Value | Designators | Role |
|---:|---|---|---|
| 20 | 10.0k | R5–R7, R9, R15–R18, R25–R28, R35–R38, R45–R48 | input summing, per-stage summing and ×2 gain pairs |
| 5 | 1.00k | R21, R22, R31, R32, R41 | ladder segments |
| 4 | 3.00k | R20, R30, R40, R42 | ladder bottom segments |
| 2 | 12.0k | R11, R12 | `OCT` ladder — **match these two to each other** above all |
| 1 | 20.0k | R8 | input summer gain, ratio with R9 |

**3.00k and 12.0k are E24, not E96, and that is deliberate.** E96 has no exact 3:1 pair —
its nearest is 3.01k against 1.00k, which is a 0.33 % ratio error and puts the 4th out by
0.66 cents. Worse, that error cannot be selected away: a 0.1 % 3.01k never measures 3.000k.
E24 values are stocked in 0.1 % thin film, so use them.

`OCT` only needs its two segments **equal to each other** — the absolute value is free,
because the trimmer sets the scale and the second tap is twice the first by construction.
A matched pair matters more than the marked value.

### 1 % is fine — 17 parts

| Qty | Value | Designators | Why tolerance does not matter |
|---:|---|---|---|
| 5 | 1.00k | R10, R19, R29, R39, R49 | output series protection |
| 4 | 49.9k | R1–R4 | reference dividers — trimmed by VR5/VR6 |
| 4 | 619R | R14, R24, R34, R44 | buffer output snubbers |
| 2 | 24.3k | R23, R33 | ladder top, absorbed by trim |
| 1 | 22.6k | R43 | ladder top, absorbed by trim |
| 1 | 5.49k | R13 | ladder top, absorbed by trim |

## Capacitors

| Qty | Value | Type | Designators | Footprint |
|---:|---|---|---|---|
| 7 | 0.1uF | X7R | C8, C11–C16 | `Capacitor_SMD:C_1206_3216Metric` |
| 4 | 330pF | C0G | C17–C20 | `Capacitor_SMD:C_1206_3216Metric` |
| 2 | 10uF | electrolytic, **ESR ≥1 Ω, mount lying flat** | C9, C10 | `Capacitor_THT:CP_Radial_D5.0mm_P2.00mm` |
| 2 | 10uF | electrolytic, any height, mounts upright | C1, C3 | `Capacitor_THT:CP_Radial_D5.0mm_P2.00mm` |
| 2 | 0.33uF | X7R | C5, C7 | `Capacitor_SMD:C_1206_3216Metric` |
| 2 | 100pF | C0G | C2, C4 | `Capacitor_SMD:C_1206_3216Metric` |
| 1 | 0.01uF | X7R | C6 | `Capacitor_SMD:C_1206_3216Metric` |

C0G on the snubbers and the HF supply caps; X7R elsewhere is fine.

**C9 and C10 must be low-profile cans; C1 and C3 need not be.** The two boards
are stacked, and the only parts inside the gap are the ones on the control
board's rear face — which is where C9 and C10 live. C1 and C3 sit on the trimmer
board's rear, facing the back of the case, where nothing constrains them.

The gap is set by the interconnect: an 8.50 mm socket body plus the 2.54 mm
plastic of the mating header puts the two boards **11.04 mm** apart. That is the
whole budget for anything on the control board's rear, and the parts already
there use:

| | height above board |
|---|---|
| U4, U5 — TO-92 | 7.30 mm |
| C9, C10 — as modelled | 5.00 mm |
| U1–U3 — SOIC-14 | 1.75 mm |
| 1206 SMD | ~0.95 mm |

A 5 mm-diameter 10 µF is sold as a **5 × 11 mm** can, and 11 mm against 11.04 mm
is no clearance at all — stood upright it will foul the trimmer board. There is
no shorter part to buy; every stocked 5 mm 10 µF is 11 mm or longer.

**So C9 and C10 are laid flat**, leads bent 90° at the board, the can resting on
the control board's rear face. On its side the same part is 5.00 mm tall — the
figure in the table above — which leaves 6 mm of clearance. Anything up to 7 mm
is safe; past that the margin is not worth having.

### C9 and C10 need ESR, and "low ESR" is the wrong part

They hang directly off U3's reference buffer outputs, wired as unity-gain
followers — the worst case for capacitive load. **The OPA4196 is rated to drive
1 nF bare. These are 10 µF, ten thousand times that.** The capacitor's own ESR is
what keeps that loop stable, so it is a specified parameter here, not a defect to
be minimised.

TI's Table 3 (SBOS869) gives the series resistance needed for a given phase
margin, and stops characterising at 1 µF:

| C load | 100 pF | 1 nF | 10 nF | 100 nF | 1 µF |
|---|---|---|---|---|---|
| R for 45° | 280 Ω | 113 Ω | 68 Ω | 17.8 Ω | 3.6 Ω |
| R for 60° | — | 432 Ω | 210 Ω | 53.6 Ω | 10 Ω |

Extrapolating one decade puts 10 µF at roughly **0.8 Ω for 45° and 2.2 Ω for
60°**. Against what each capacitor type actually offers:

| Type, 10 µF | ESR | |
|---|---|---|
| ceramic X7R 1210 | 2–10 mΩ | ~200× too low |
| polymer tantalum, polymer aluminium | 20–100 mΩ | still far too low |
| **MnO2 tantalum, EIA-3528** | 0.5–3 Ω | in range |
| **aluminium electrolytic, 5 mm** | 1–3 Ω | in range |

So **do not substitute a ceramic, a polymer tantalum, or a "low ESR" aluminium
part here.** All three are marketed as upgrades and all three remove the damping.
An ordinary aluminium electrolytic — the last row of that table, and what the
board's through-hole footprint expects — sits squarely in range. Height is dealt
with by laying the can flat, as above, not by picking a different chemistry.

The ESR must be in the capacitor rather than a discrete resistor, even though TI
recommends the resistor. An isolation resistor sits between the amplifier output
and *everything*, so the ladder current flows through it: worst case is four
30 kΩ ladders selecting the positive reference, 333 µA. At the 10 Ω TI lists for
1 µF that is 3.3 mV of reference shift, moving the `OCT_2V` tap by 3.2 cents —
and the shift tracks how many switches point up, so it is not a fixed offset and
cannot be trimmed out. The capacitor's ESR carries no DC load current at all,
because the ladders connect to the amplifier output directly.

## Semiconductors

| Qty | Part | Designators | Footprint |
|---:|---|---|---|
| 3 | OPA4196 (SOIC-14) | U1, U2, U3 | `Package_SO:SOIC-14_3.9x8.7mm_P1.27mm` |
| 1 | L78L05 | U4 | `Package_TO_SOT_THT:TO-92_Inline` |
| 1 | L79L05 | U5 | `Package_TO_SOT_THT:TO-92_Inline` |
| 2 | 1N5819 | D1, D2 | `Diode_THT:D_DO-41_SOD81_P10.16mm_Horizontal` |

**The two regulators do not share a pinout.** L78L05 TO-92 is `1 = VOUT, 2 = GND, 3 = VIN`;
L79L05 is `1 = GND, 2 = VIN, 3 = VOUT`. Both datasheet figures are *bottom* views — check
the footprint's pad 1 against the datasheet with the part oriented as you will fit it.

## Electromechanical

| Qty | Part | Designators | Footprint |
|---:|---|---|---|
| 8 | Thonkiconn PJ398SM | J1–J8 | `eurorack:Thonkiconn_PJ301M` |
| 4 | Taiway `200-MSP3-T1B1M2QE` SPDT ON-OFF-ON | SW1–SW4 | `eurorack:SW_Taiway_200_SPDT` |
| 3 | Taiway `200-MDP6-T1B1M2QE` DPDT ON-ON-ON | SW6, SW7, SW8 | `eurorack:SW_Taiway_200_DPDT` |
| 1 | Taiway `200-MSP1-T1B1M2QE` SPDT ON-ON | SW5 | `eurorack:SW_Taiway_200_SPDT` |
| 4 | 1k multiturn trimmer | VR1–VR4 | `Potentiometer_THT:Potentiometer_Bourns_3296W_Vertical` |
| 2 | 50k multiturn trimmer | VR5, VR6 | `Potentiometer_THT:Potentiometer_Bourns_3296W_Vertical` |
| 2 | Ferrite bead, axial | FB1, FB2 | `Resistor_THT:R_Axial_DIN0207_L6.3mm_D2.5mm_P7.62mm_Horizontal` |
| 1 | Eurorack 2×5 shrouded header | P1 | `Connector_IDC:IDC-Header_2x05_P2.54mm_Vertical` |
| 4 | 1×6 pin header, 2.54 mm | P2–P5 | `Connector_PinHeader_2.54mm:PinHeader_1x06_P2.54mm_Vertical` |
| 4 | 1×6 socket, 2.54 mm | P6–P9 | `Connector_PinSocket_2.54mm:PinSocket_1x06_P2.54mm_Vertical` |

Keep the **shrouded, keyed** power header — it is the only thing that stops the ribbon
going on backwards, and D1/D2 are the last line of defence after it.

### Board-to-board interconnect
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
